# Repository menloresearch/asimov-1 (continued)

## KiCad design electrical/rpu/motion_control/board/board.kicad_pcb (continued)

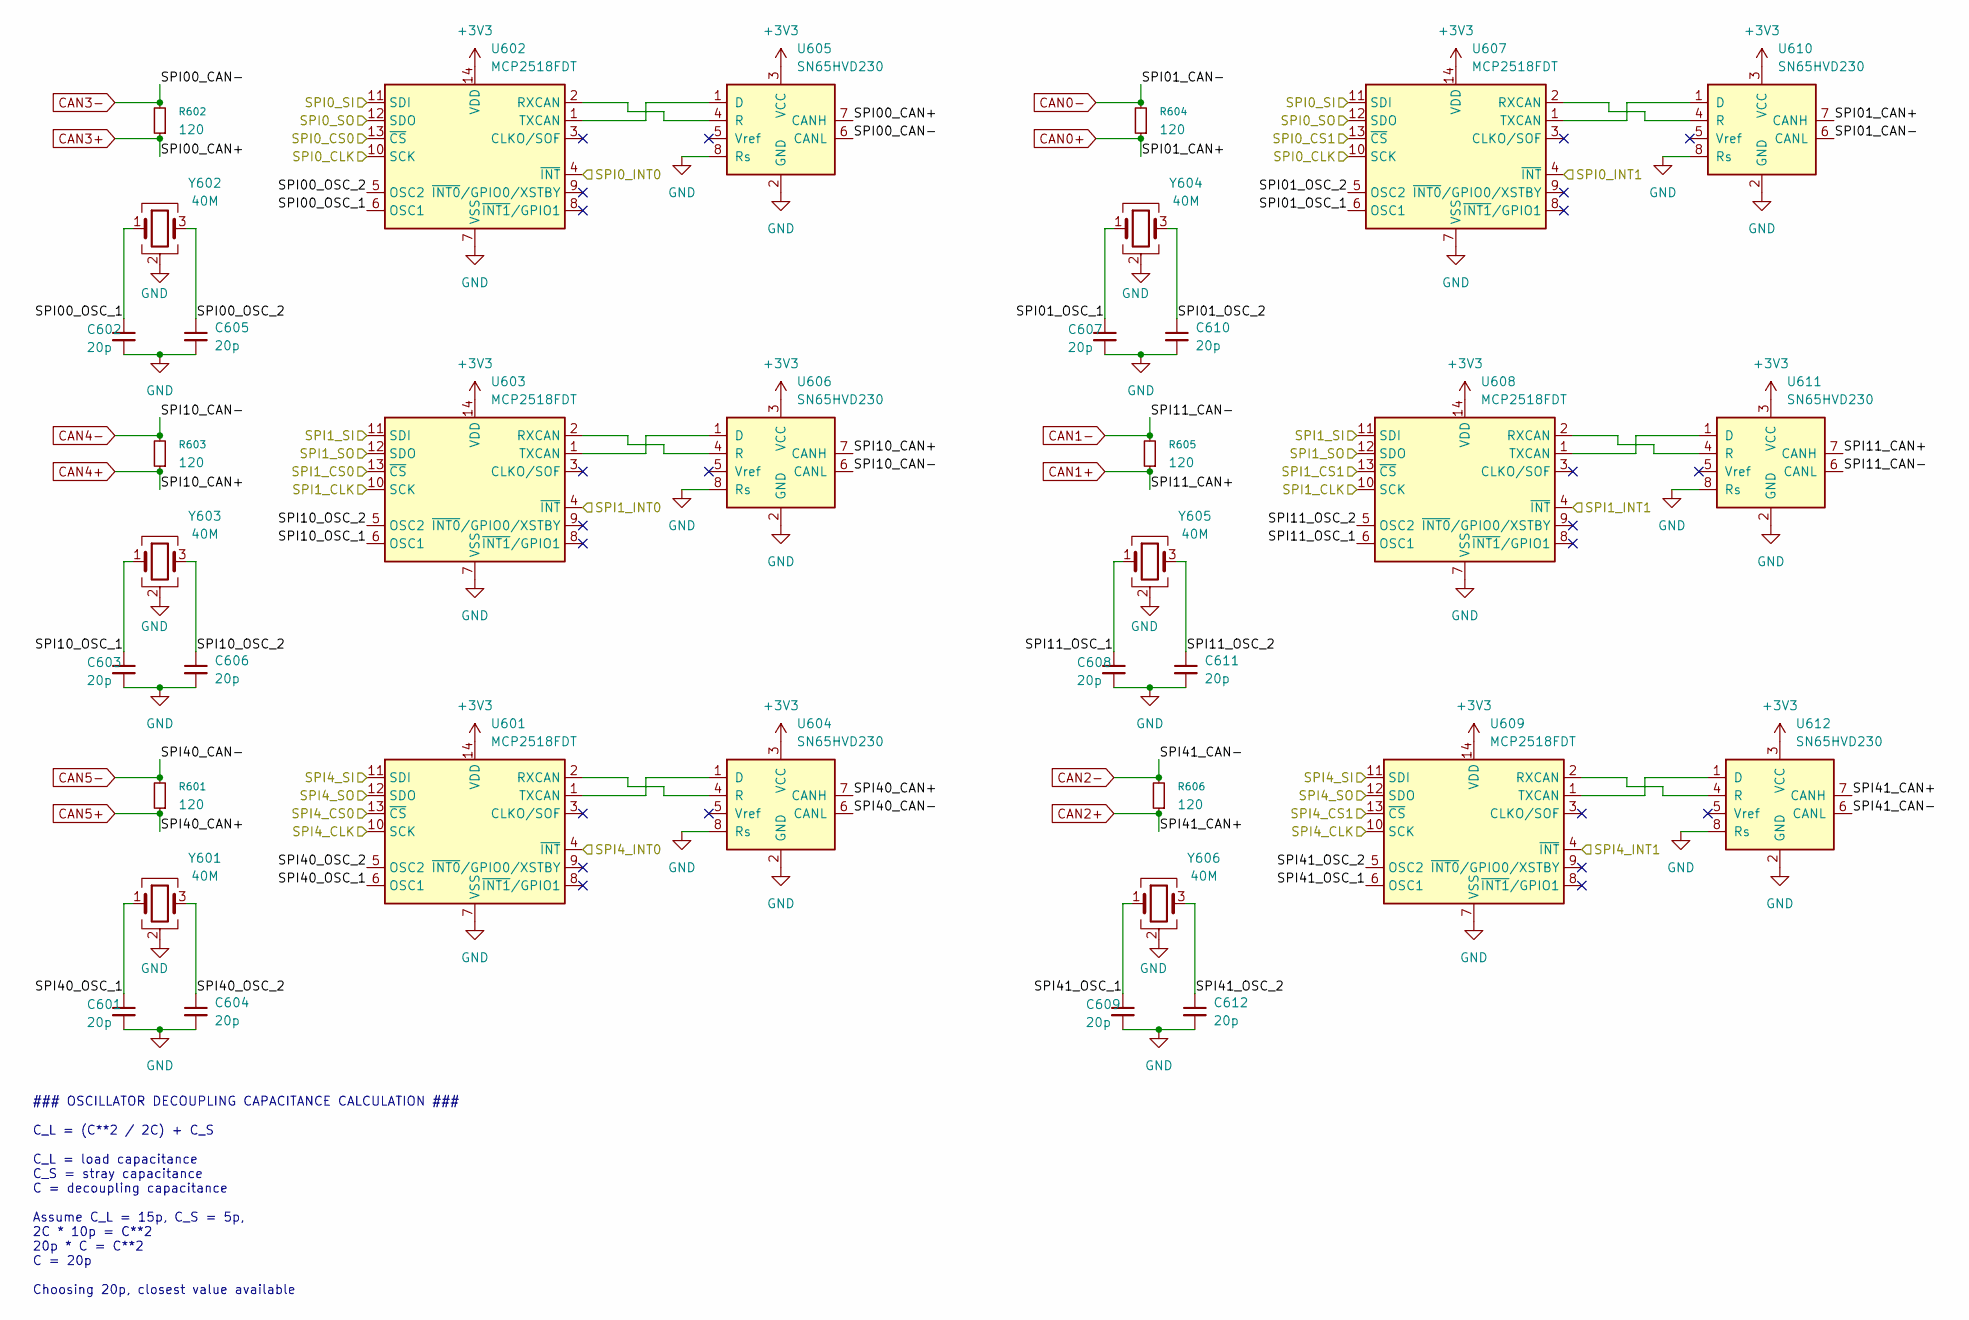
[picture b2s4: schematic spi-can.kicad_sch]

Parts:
C601, C602, C603, C604, C605, C606, C607, C608, C609, C610, C611, C612: 20p; C_0603_1608Metric; LCSC C165732
R601, R602, R603, R604, R605, R606: 120; R_0402_1005Metric; LCSC C114758
U601, U602, U603, U607, U608, U609: MCP2518FDT; SOIC-14_3.9x8.7mm_P1.27mm
U604, U605, U606, U610, U611, U612: SN65HVD230; SOIC-8_3.9x4.9mm_P1.27mm; LCSC C12084
Y601, Y602, Y603, Y604, Y605, Y606: 40M; Crystal_SMD_3225-4Pin_3.2x2.5mm; LCSC C7473041

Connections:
+3V3: U601.14 (VDD), U602.14 (VDD), U603.14 (VDD), U604.3 (VCC), U605.3 (VCC), U606.3 (VCC), U607.14 (VDD), U608.14 (VDD), U609.14 (VDD), U610.3 (VCC), U611.3 (VCC), U612.3 (VCC); also elsewhere on the board
/J1/SPI1_CS0: U603.13 (~CS); also elsewhere on the board
/J1/SPI1_CS1: U608.13 (~CS); also elsewhere on the board
/J1/SPI1_INT0: U603.4 (~INT); also elsewhere on the board
/J1/SPI1_INT1: U608.4 (~INT); also elsewhere on the board
/J1/SPI4_CS0: U601.13 (~CS); also elsewhere on the board
/J1/SPI4_CS1: U609.13 (~CS); also elsewhere on the board
/J1/SPI4_INT0: U601.4 (~INT); also elsewhere on the board
/J1/SPI4_INT1: U609.4 (~INT); also elsewhere on the board
/SPI-CAN/SPI0_CLK: U602.10 (SCK), U607.10 (SCK); also elsewhere on the board
/SPI-CAN/SPI0_CS0: U602.13 (~CS); also elsewhere on the board
/SPI-CAN/SPI0_CS1: U607.13 (~CS); also elsewhere on the board
/SPI-CAN/SPI0_INT0: U602.4 (~INT); also elsewhere on the board
/SPI-CAN/SPI0_INT1: U607.4 (~INT); also elsewhere on the board
/SPI-CAN/SPI00_OSC_1: C602.1, U602.6 (OSC1), Y602.1
/SPI-CAN/SPI00_OSC_2: C605.1, U602.5 (OSC2), Y602.3
/SPI-CAN/SPI0_SI: U602.11 (SDI), U607.11 (SDI); also elsewhere on the board
/SPI-CAN/SPI0_SO: U602.12 (SDO), U607.12 (SDO); also elsewhere on the board
/SPI-CAN/SPI1_CLK: U603.10 (SCK), U608.10 (SCK); also elsewhere on the board
/SPI-CAN/SPI01_OSC_1: C607.1, U607.6 (OSC1), Y604.1
/SPI-CAN/SPI01_OSC_2: C610.1, U607.5 (OSC2), Y604.3
/SPI-CAN/SPI1_SI: U603.11 (SDI), U608.11 (SDI); also elsewhere on the board
/SPI-CAN/SPI1_SO: U603.12 (SDO), U608.12 (SDO); also elsewhere on the board
/SPI-CAN/SPI4_CLK: U601.10 (SCK), U609.10 (SCK); also elsewhere on the board
/SPI-CAN/SPI4_SI: U601.11 (SDI), U609.11 (SDI); also elsewhere on the board
/SPI-CAN/SPI4_SO: U601.12 (SDO), U609.12 (SDO); also elsewhere on the board
/SPI-CAN/SPI10_OSC_1: C603.1, U603.6 (OSC1), Y603.1
/SPI-CAN/SPI10_OSC_2: C606.1, U603.5 (OSC2), Y603.3
/SPI-CAN/SPI11_OSC_1: C608.1, U608.6 (OSC1), Y605.1
/SPI-CAN/SPI11_OSC_2: C611.1, U608.5 (OSC2), Y605.3
/SPI-CAN/SPI40_OSC_1: C601.1, U601.6 (OSC1), Y601.1
/SPI-CAN/SPI40_OSC_2: C604.1, U601.5 (OSC2), Y601.3
/SPI-CAN/SPI41_OSC_1: C609.1, U609.6 (OSC1), Y606.1
/SPI-CAN/SPI41_OSC_2: C612.1, U609.5 (OSC2), Y606.3
CAN0+: R604.1, U610.7 (CANH); also elsewhere on the board
CAN0-: R604.2, U610.6 (CANL); also elsewhere on the board
CAN1+: R605.1, U611.7 (CANH); also elsewhere on the board
CAN1-: R605.2, U611.6 (CANL); also elsewhere on the board
CAN2+: R606.1, U612.7 (CANH); also elsewhere on the board
CAN2-: R606.2, U612.6 (CANL); also elsewhere on the board
CAN3+: R602.1, U605.7 (CANH); also elsewhere on the board
CAN3-: R602.2, U605.6 (CANL); also elsewhere on the board
CAN4+: R603.1, U606.7 (CANH); also elsewhere on the board
CAN4-: R603.2, U606.6 (CANL); also elsewhere on the board
CAN5+: R601.1, U604.7 (CANH); also elsewhere on the board
CAN5-: R601.2, U604.6 (CANL); also elsewhere on the board
GND: C601.2, C602.2, C603.2, C604.2, C605.2, C606.2, C607.2, C608.2, C609.2, C610.2, C611.2, C612.2, U601.7 (VSS), U601.15 (VSS), U602.7 (VSS), U602.15 (VSS), U603.7 (VSS), U603.15 (VSS), U604.2 (GND), U604.8 (Rs), U605.2 (GND), U605.8 (Rs), U606.2 (GND), U606.8 (Rs), U607.7 (VSS), U607.15 (VSS), U608.7 (VSS), U608.15 (VSS), U609.7 (VSS), U609.15 (VSS), U610.2 (GND), U610.8 (Rs), U611.2 (GND), U611.8 (Rs), U612.2 (GND), U612.8 (Rs), Y601.2 (G), Y601.4 (G), Y602.2 (G), Y602.4 (G), Y603.2 (G), Y603.4 (G), Y604.2 (G), Y604.4 (G), Y605.2 (G), Y605.4 (G), Y606.2 (G), Y606.4 (G); also elsewhere on the board
unnamed: U601.2 (RXCAN), U604.4 (R)
unnamed: U601.1 (TXCAN), U604.1 (D)
unnamed: U602.2 (RXCAN), U605.4 (R)
unnamed: U602.1 (TXCAN), U605.1 (D)
unnamed: U603.2 (RXCAN), U606.4 (R)
unnamed: U603.1 (TXCAN), U606.1 (D)
unnamed: U607.2 (RXCAN), U610.4 (R)
unnamed: U607.1 (TXCAN), U610.1 (D)
unnamed: U608.2 (RXCAN), U611.4 (R)
unnamed: U608.1 (TXCAN), U611.1 (D)
unnamed: U609.2 (RXCAN), U612.4 (R)
unnamed: U609.1 (TXCAN), U612.1 (D)

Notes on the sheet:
### OSCILLATOR DECOUPLING CAPACITANCE CALCULATION ### C_L = (C**2 / 2C) + C_S C_L = load capacitance C_S = stray capacitance C = decoupling capacitance Assume C_L = 15p, C_S = 5p, 2C * 10p = C**2 20p * C = C**2 C = 20p Choosing 20p, closest value available

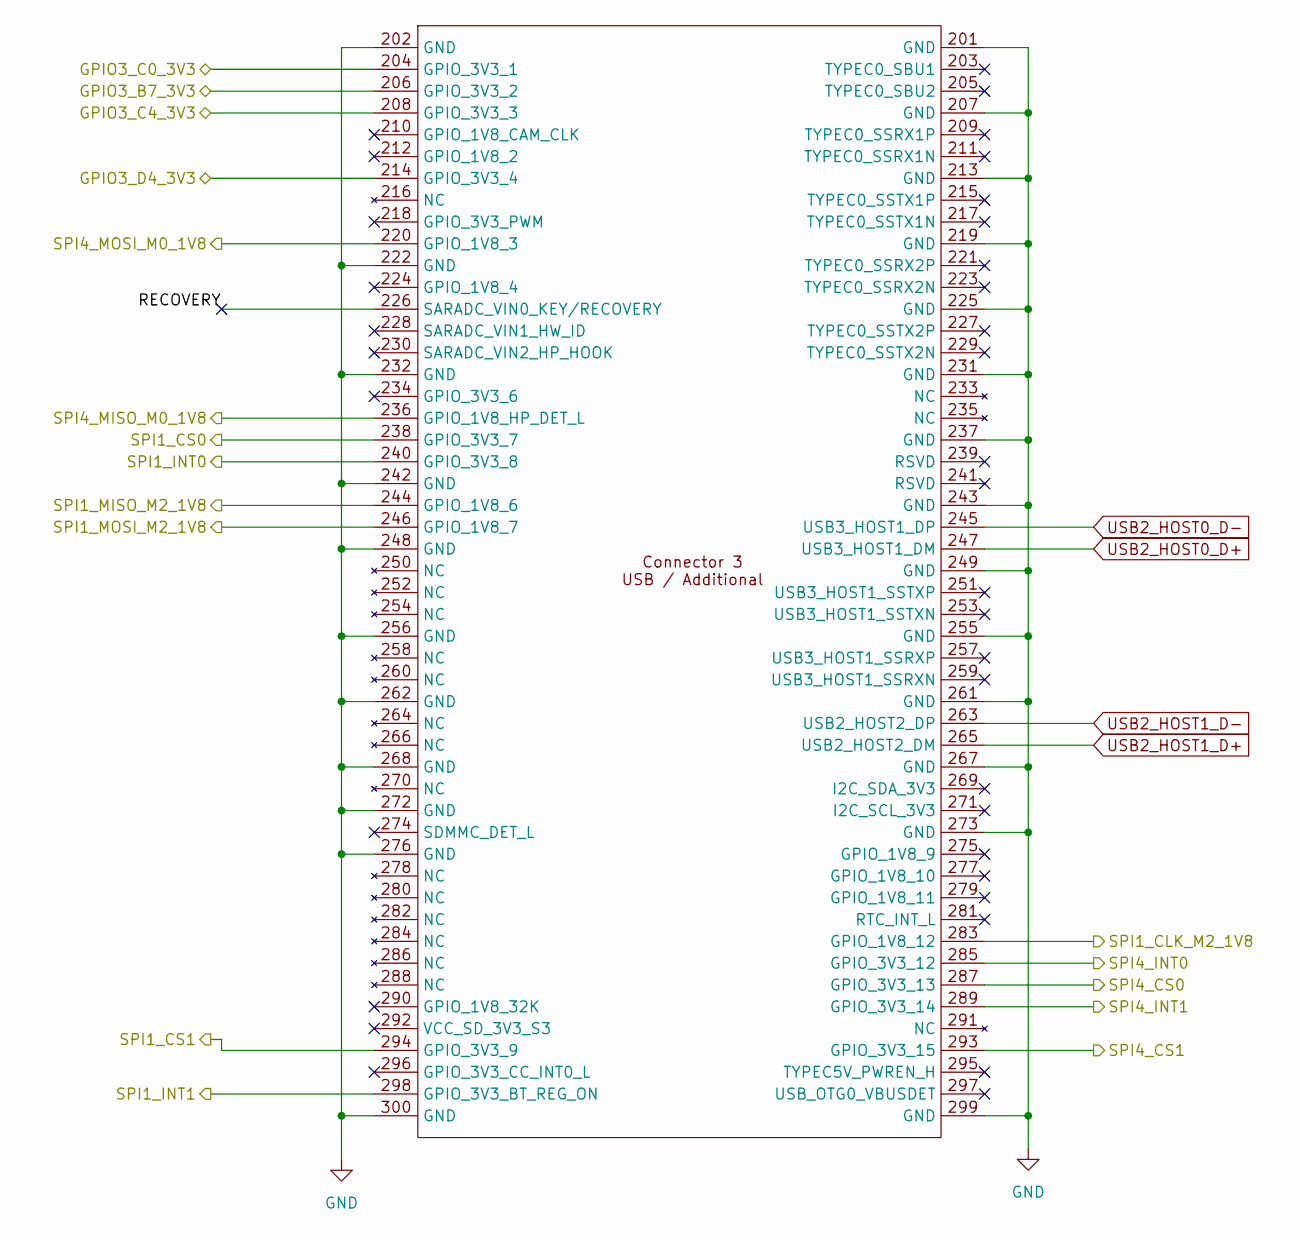
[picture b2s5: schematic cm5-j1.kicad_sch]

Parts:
U401: Hirose DF40C-100DS-0.4V; radxa_cm5_3; LCSC C597931

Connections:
/J1/GPIO3_B7_3V3: U401.206 (GPIO_3V3_2); also elsewhere on the board
/J1/GPIO3_C0_3V3: U401.204 (GPIO_3V3_1); also elsewhere on the board
/J1/GPIO3_C4_3V3: U401.208 (GPIO_3V3_3); also elsewhere on the board
/J1/GPIO3_D4_3V3: U401.214 (GPIO_3V3_4); also elsewhere on the board
/J1/RECOVERY: U401.226 (SARADC_VIN0_KEY/RECOVERY)
/J1/SPI1_CLK_M2_1V8: U401.283 (GPIO_1V8_12); also elsewhere on the board
/J1/SPI1_CS0: U401.238 (GPIO_3V3_7); also elsewhere on the board
/J1/SPI1_CS1: U401.294 (GPIO_3V3_9); also elsewhere on the board
/J1/SPI1_INT0: U401.240 (GPIO_3V3_8); also elsewhere on the board
/J1/SPI1_INT1: U401.298 (GPIO_3V3_BT_REG_ON); also elsewhere on the board
/J1/SPI1_MISO_M2_1V8: U401.244 (GPIO_1V8_6); also elsewhere on the board
/J1/SPI1_MOSI_M2_1V8: U401.246 (GPIO_1V8_7); also elsewhere on the board
/J1/SPI4_CS0: U401.287 (GPIO_3V3_13); also elsewhere on the board
/J1/SPI4_CS1: U401.293 (GPIO_3V3_15); also elsewhere on the board
/J1/SPI4_INT0: U401.285 (GPIO_3V3_12); also elsewhere on the board
/J1/SPI4_INT1: U401.289 (GPIO_3V3_14); also elsewhere on the board
/J1/SPI4_MISO_M0_1V8: U401.236 (GPIO_1V8_HP_DET_L); also elsewhere on the board
/J1/SPI4_MOSI_M0_1V8: U401.220 (GPIO_1V8_3); also elsewhere on the board
GND: U401.201 (GND), U401.202 (GND), U401.207 (GND), U401.213 (GND), U401.219 (GND), U401.222 (GND), U401.225 (GND), U401.231 (GND), U401.232 (GND), U401.237 (GND), U401.242 (GND), U401.243 (GND), U401.248 (GND), U401.249 (GND), U401.255 (GND), U401.256 (GND), U401.261 (GND), U401.262 (GND), U401.267 (GND), U401.268 (GND), U401.272 (GND), U401.273 (GND), U401.276 (GND), U401.299 (GND), U401.300 (GND); also elsewhere on the board
USB2_HOST0_D+: U401.247 (USB3_HOST1_DM); also elsewhere on the board
USB2_HOST0_D-: U401.245 (USB3_HOST1_DP); also elsewhere on the board
USB2_HOST1_D+: U401.265 (USB2_HOST2_DM); also elsewhere on the board
USB2_HOST1_D-: U401.263 (USB2_HOST2_DP); also elsewhere on the board

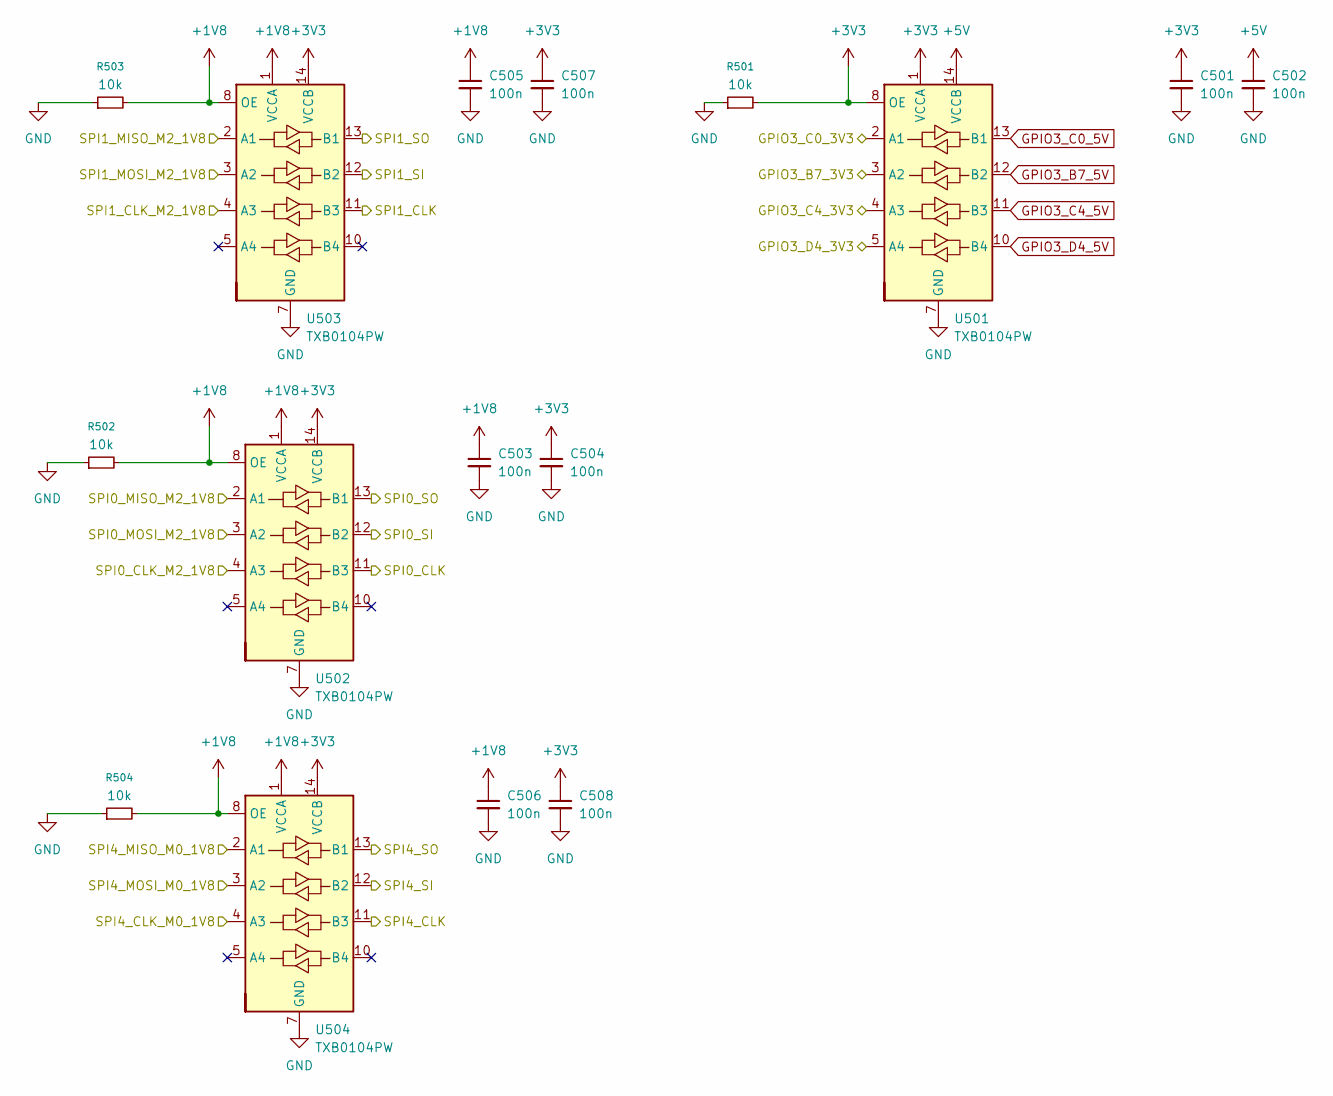
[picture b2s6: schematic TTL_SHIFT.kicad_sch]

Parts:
C501, C502, C503, C504, C505, C506, C507, C508: 100n; C_0402_1005Metric; LCSC C77020
R501, R502, R503, R504: 10k; R_0402_1005Metric; LCSC C190095
U501, U502, U503, U504: TXB0104PW; TSSOP-14_4.4x5mm_P0.65mm; LCSC C60708

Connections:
+1V8: C503.1, C505.1, C506.1, R502.2, R503.2, R504.2, U502.1 (VCCA), U502.8 (OE), U503.1 (VCCA), U503.8 (OE), U504.1 (VCCA), U504.8 (OE); also elsewhere on the board
+3V3: C501.1, C504.1, C507.1, C508.1, R501.2, U501.1 (VCCA), U501.8 (OE), U502.14 (VCCB), U503.14 (VCCB), U504.14 (VCCB); also elsewhere on the board
+5V: C502.1, U501.14 (VCCB); also elsewhere on the board
/J1/GPIO3_B7_3V3: U501.3 (A2); also elsewhere on the board
/J1/GPIO3_C0_3V3: U501.2 (A1); also elsewhere on the board
/J1/GPIO3_C4_3V3: U501.4 (A3); also elsewhere on the board
/J1/GPIO3_D4_3V3: U501.5 (A4); also elsewhere on the board
/J1/SPI1_CLK_M2_1V8: U503.4 (A3); also elsewhere on the board
/J1/SPI1_MISO_M2_1V8: U503.2 (A1); also elsewhere on the board
/J1/SPI1_MOSI_M2_1V8: U503.3 (A2); also elsewhere on the board
/J1/SPI4_MISO_M0_1V8: U504.2 (A1); also elsewhere on the board
/J1/SPI4_MOSI_M0_1V8: U504.3 (A2); also elsewhere on the board
/SPI-CAN/SPI0_CLK: U502.11 (B3); also elsewhere on the board
/SPI-CAN/SPI0_SI: U502.12 (B2); also elsewhere on the board
/SPI-CAN/SPI0_SO: U502.13 (B1); also elsewhere on the board
/SPI-CAN/SPI1_CLK: U503.11 (B3); also elsewhere on the board
/SPI-CAN/SPI1_SI: U503.12 (B2); also elsewhere on the board
/SPI-CAN/SPI1_SO: U503.13 (B1); also elsewhere on the board
/SPI-CAN/SPI4_CLK: U504.11 (B3); also elsewhere on the board
/SPI-CAN/SPI4_SI: U504.12 (B2); also elsewhere on the board
/SPI-CAN/SPI4_SO: U504.13 (B1); also elsewhere on the board
/TTL-SHIFT/SPI0_CLK_M2_1V8: U502.4 (A3); also elsewhere on the board
/TTL-SHIFT/SPI0_MISO_M2_1V8: U502.2 (A1); also elsewhere on the board
/TTL-SHIFT/SPI0_MOSI_M2_1V8: U502.3 (A2); also elsewhere on the board
/TTL-SHIFT/SPI4_CLK_M0_1V8: U504.4 (A3); also elsewhere on the board
GND: C501.2, C502.2, C503.2, C504.2, C505.2, C506.2, C507.2, C508.2, R501.1, R502.1, R503.1, R504.1, U501.7 (GND), U502.7 (GND), U503.7 (GND), U504.7 (GND); also elsewhere on the board
GPIO3_B7_5V: U501.12 (B2); also elsewhere on the board
GPIO3_C0_5V: U501.13 (B1); also elsewhere on the board
GPIO3_C4_5V: U501.11 (B3); also elsewhere on the board
GPIO3_D4_5V: U501.10 (B4); also elsewhere on the board

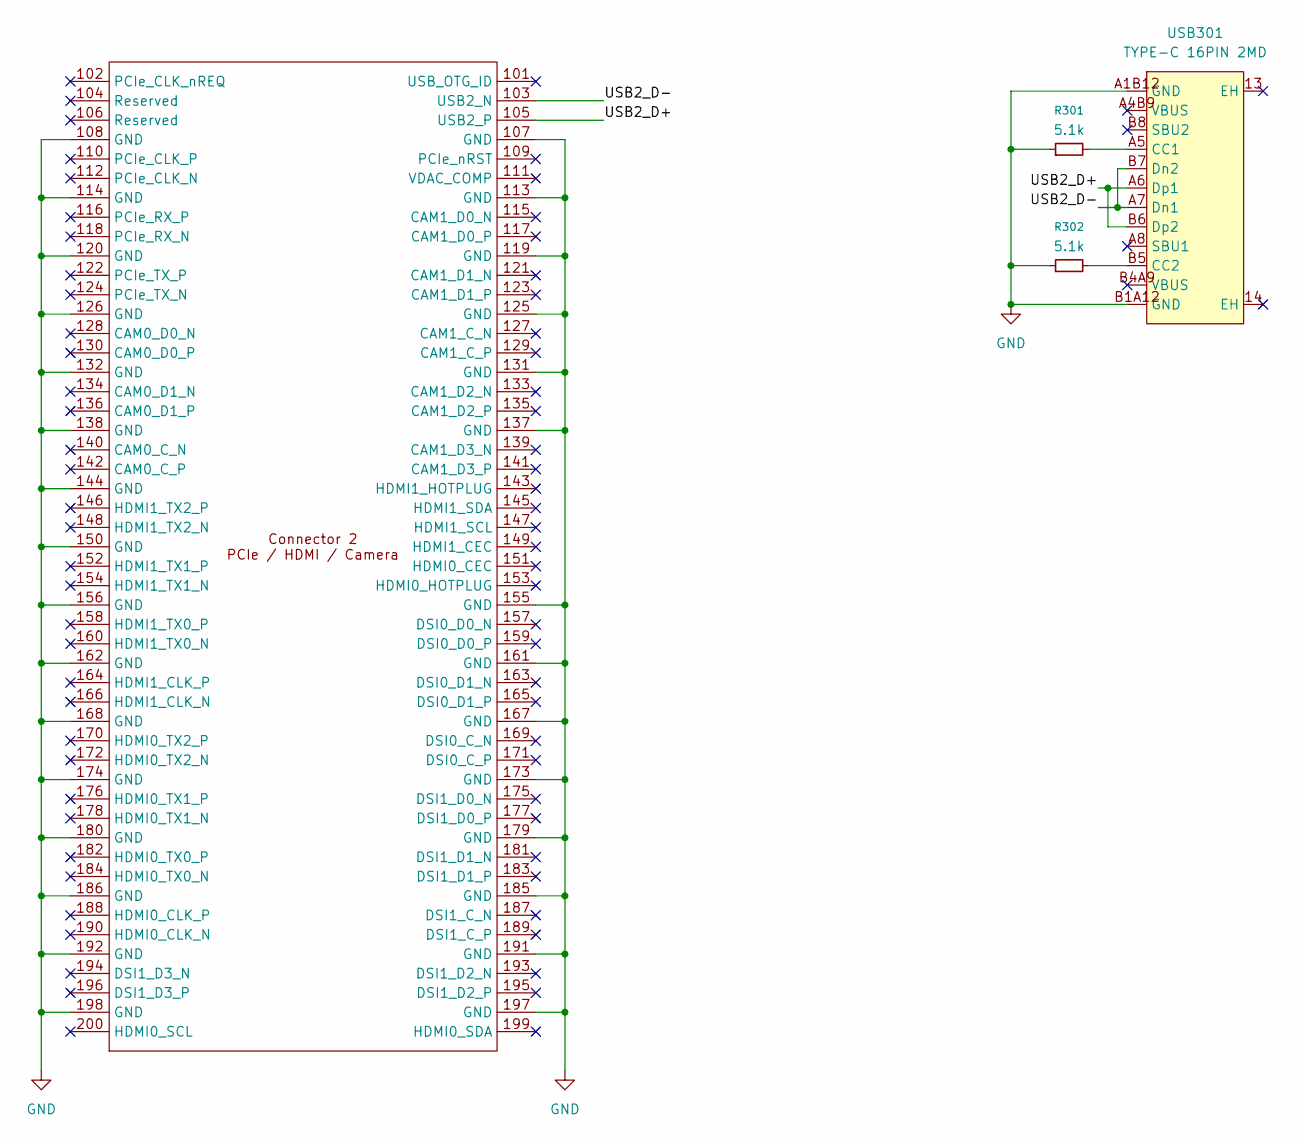
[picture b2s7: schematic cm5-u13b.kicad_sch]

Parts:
R301, R302: 5.1k; R_0402_1005Metric; LCSC C105872
U301: Hirose DF40C-100DS-0.4V; radxa_cm5_2; LCSC C597931
USB301: TYPE-C 16PIN 2MD; USB-C-SMD_TYPE-C-16PIN-2MD-073; MPN TYPE-C 16PIN 2MD(073); LCSC Part C2765186

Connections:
/U13B/USB2_D+: U301.105 (USB2_P), USB301.A6 (Dp1), USB301.B6 (Dp2)
/U13B/USB2_D-: U301.103 (USB2_N), USB301.A7 (Dn1), USB301.B7 (Dn2)
GND: R301.1, R302.1, U301.107 (GND), U301.108 (GND), U301.113 (GND), U301.114 (GND), U301.119 (GND), U301.120 (GND), U301.125 (GND), U301.126 (GND), U301.131 (GND), U301.132 (GND), U301.137 (GND), U301.138 (GND), U301.144 (GND), U301.150 (GND), U301.155 (GND), U301.156 (GND), U301.161 (GND), U301.162 (GND), U301.167 (GND), U301.168 (GND), U301.173 (GND), U301.174 (GND), U301.179 (GND), U301.180 (GND), U301.185 (GND), U301.186 (GND), U301.191 (GND), U301.192 (GND), U301.197 (GND), U301.198 (GND), USB301.A1B12 (GND), USB301.B1A12 (GND); also elsewhere on the board
unnamed: R301.2, USB301.A5 (CC1)
unnamed: R302.2, USB301.B5 (CC2)

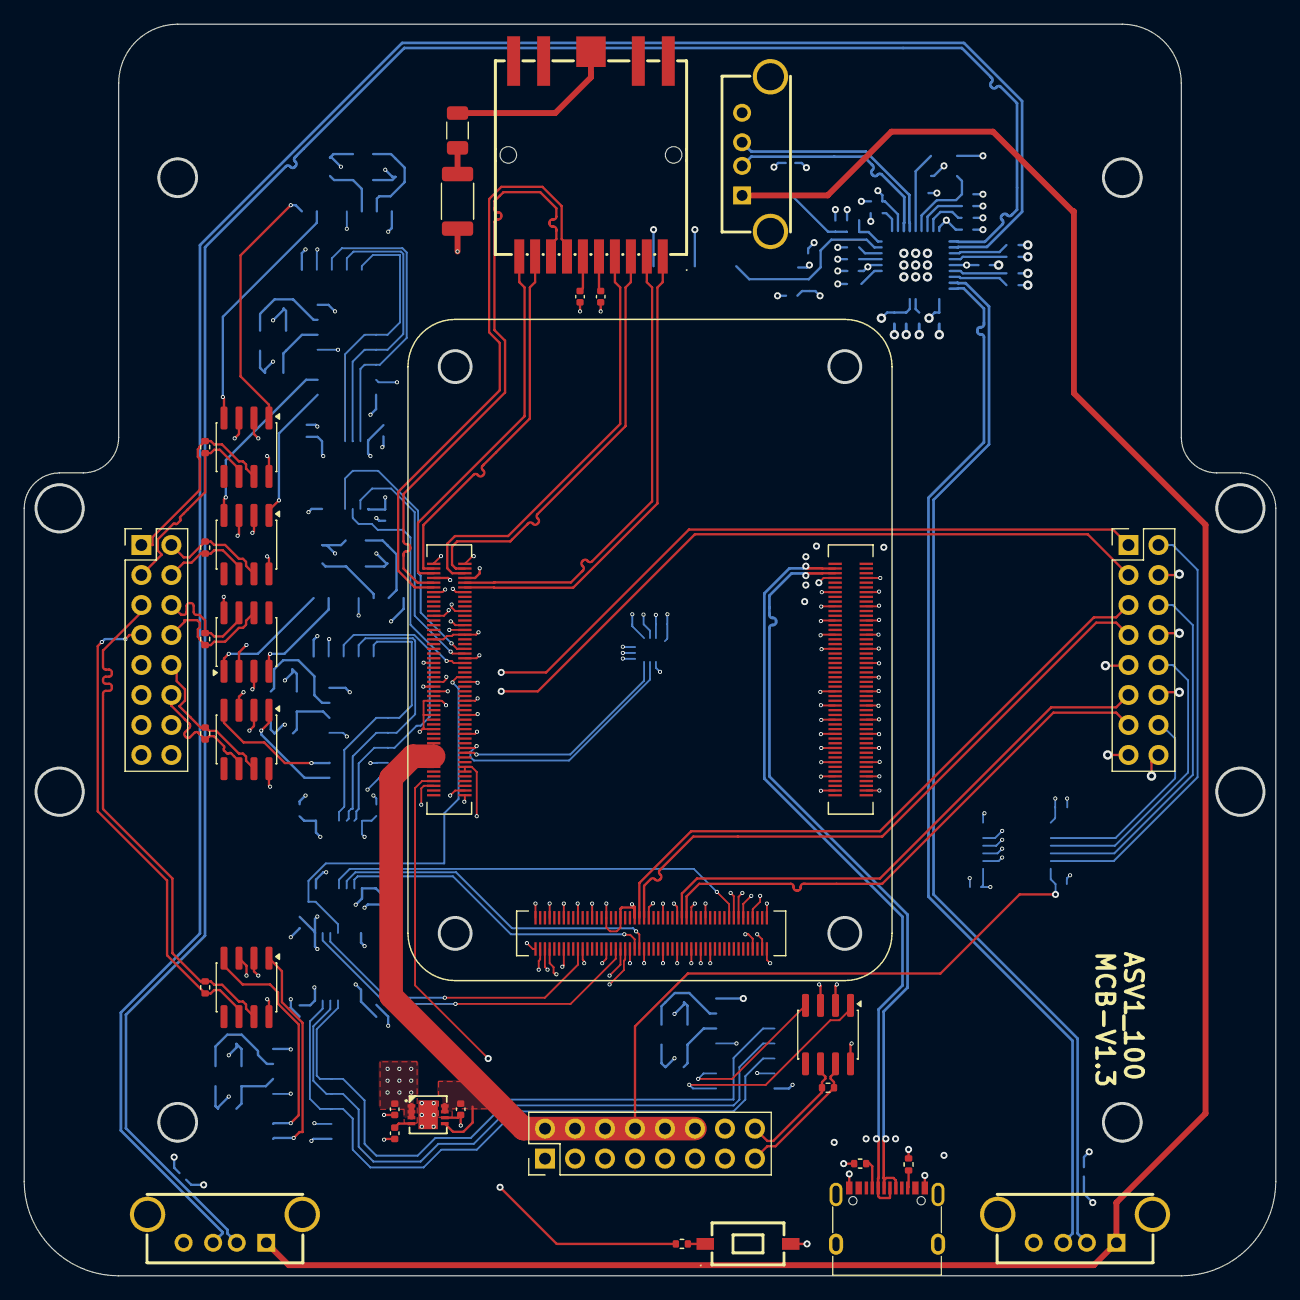
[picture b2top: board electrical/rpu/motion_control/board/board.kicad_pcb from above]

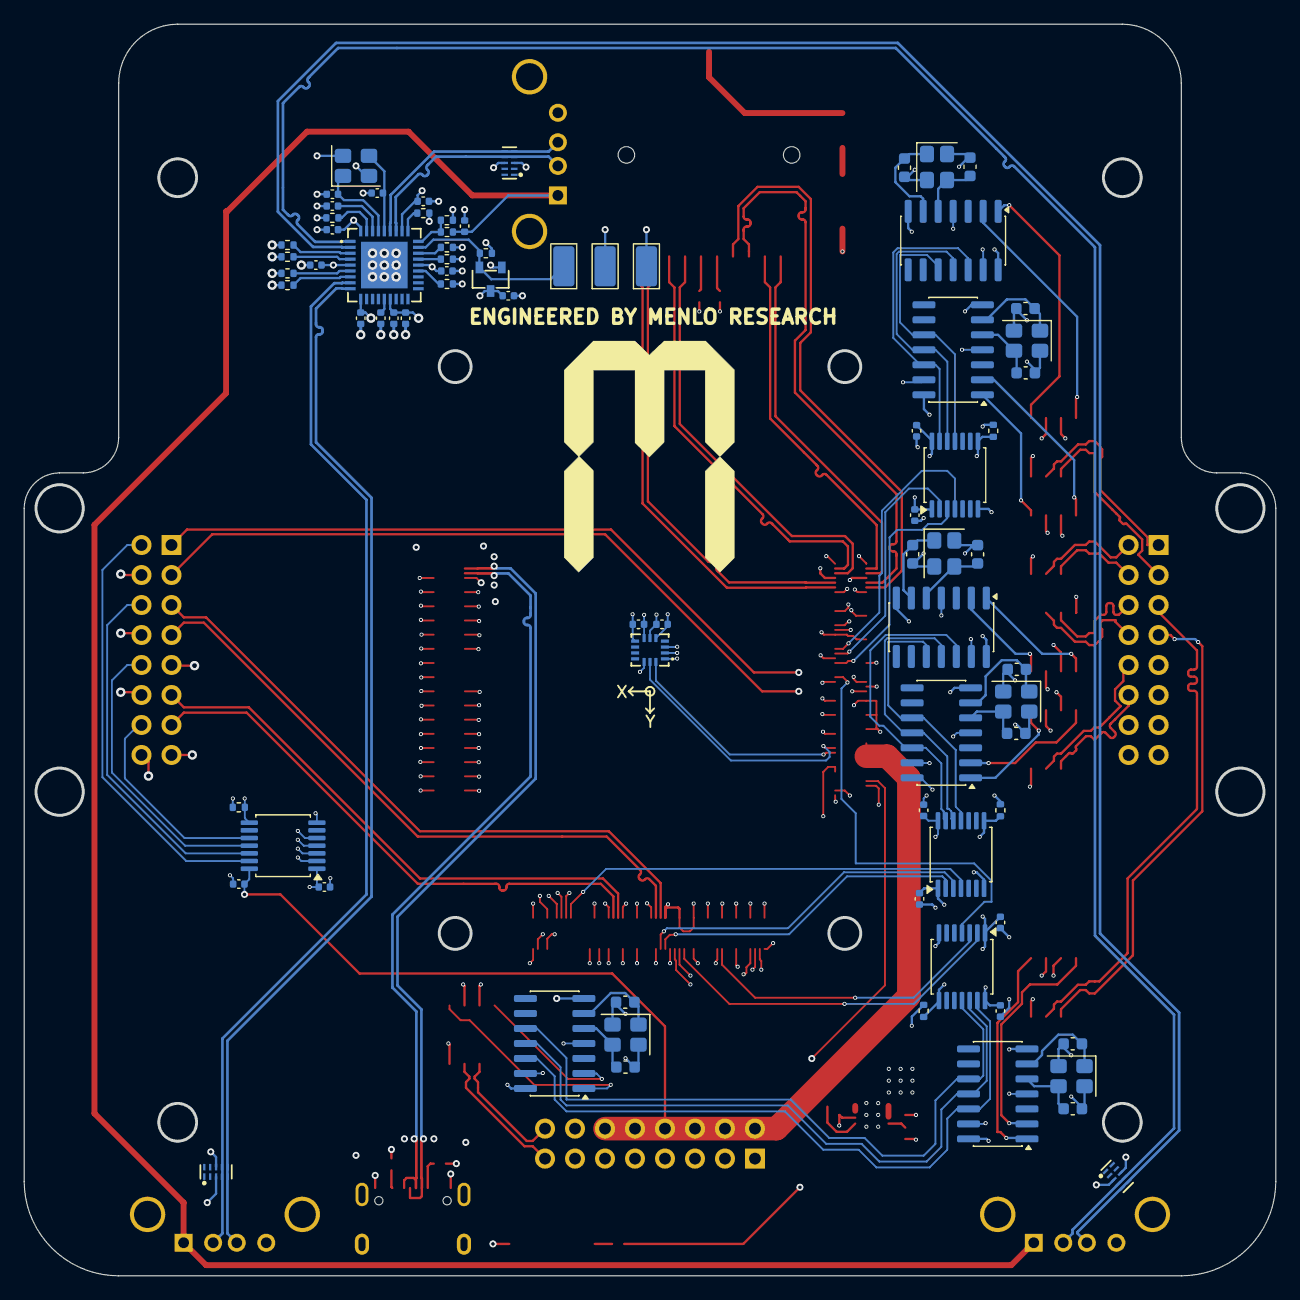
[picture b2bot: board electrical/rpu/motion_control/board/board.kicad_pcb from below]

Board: 4 copper layers, 106.0 x 106.0 mm, 112 parts (77 on the bottom side), 127 nets.

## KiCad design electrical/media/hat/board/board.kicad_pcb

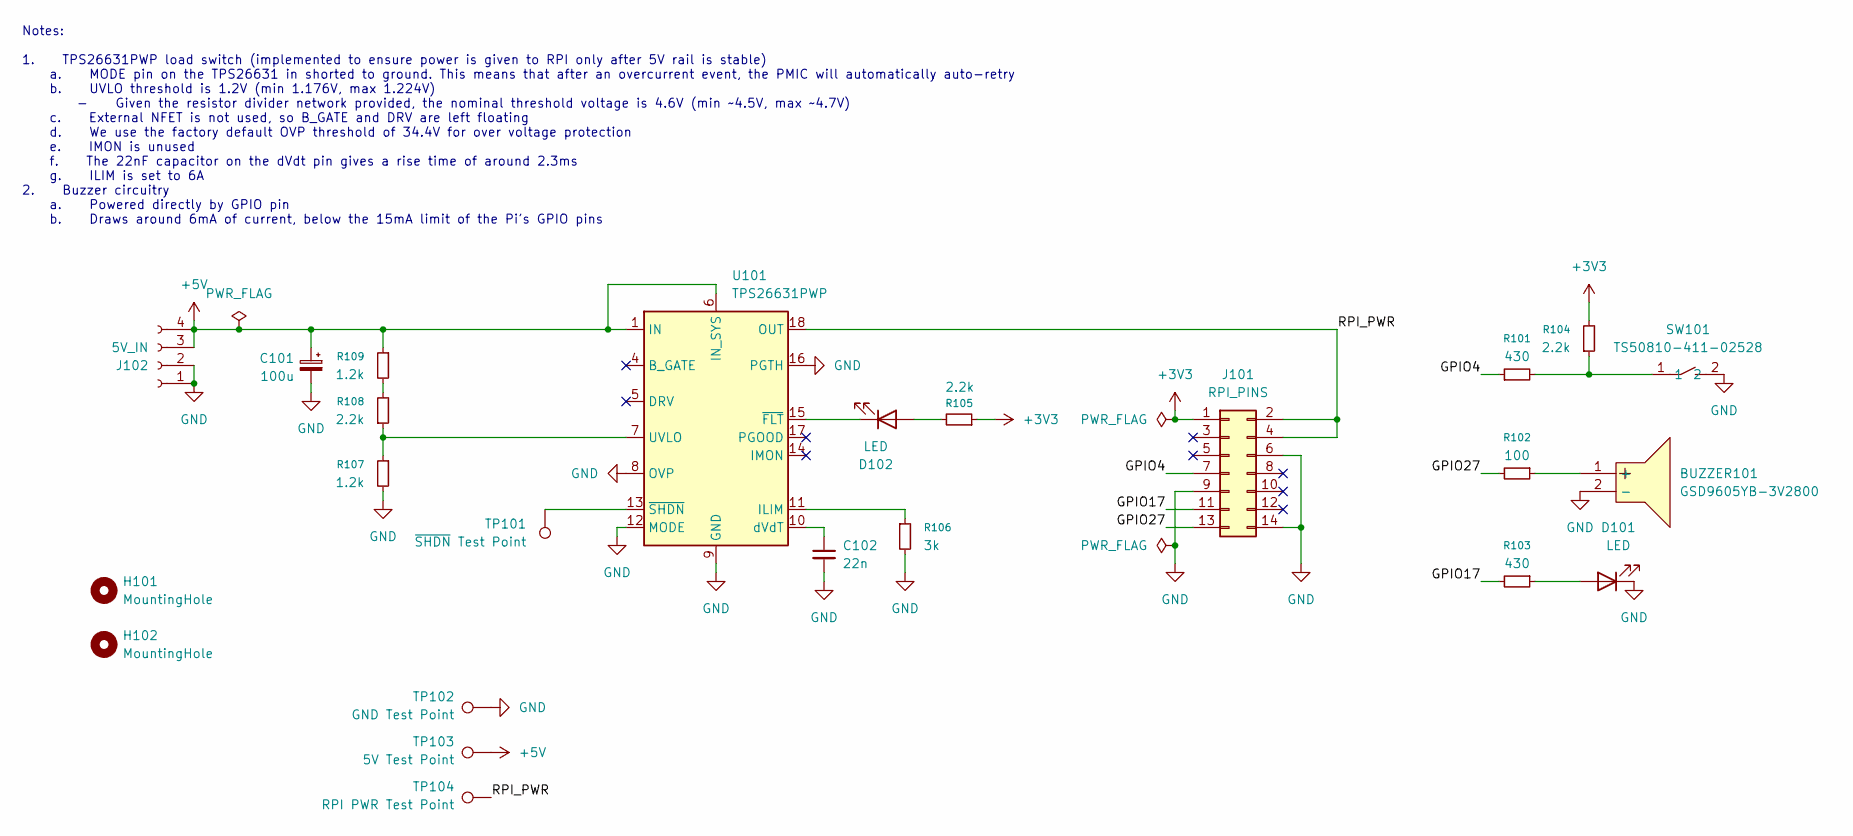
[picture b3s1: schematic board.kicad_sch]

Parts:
BUZZER101: GSD9605YB-3V2800; BUZ-SMD_GSD9605YB-3V2800; MPN GSD9605YB-3V2800; LCSC Part C255327
C101: 100u; CP_EIA-7343-31_Kemet-D; LCSC C600555
C102: 22n; C_0402_1005Metric; LCSC C1532
D101, D102: LED; LED_0603_1608Metric; LCSC C965804
H101, H102: MountingHole; MountingHole_2.5mm
J101: RPI_PINS; PinSocket_2x07_P2.54mm_Vertical; LCSC C5116484
J102: 5V_IN; JST_XH_B4B-XH-A_1x04_P2.50mm_Vertical; LCSC C144395
R101, R103: 430; R_0402_1005Metric; LCSC C137868
R102: 100; R_0402_1005Metric; LCSC C25076
R104, R105, R108: 2.2k; R_0402_1005Metric; LCSC C25879
R106: 3k; R_0603_1608Metric; LCSC C4211
R107, R109: 1.2k; R_0402_1005Metric; LCSC C2909307
SW101: TS50810-411-02528; SW-SMD_L6.2-W3.7-LS8.0; MPN TS50810-411-02528; LCSC Part C42400876
TP101: ~{SHDN} Test Point; TestPoint_Keystone_5015_Micro_Mini; LCSC C5199798
TP102: GND Test Point; TestPoint_Keystone_5015_Micro_Mini; LCSC C5199798
TP103: 5V Test Point; TestPoint_Keystone_5015_Micro_Mini; LCSC C5199798
TP104: RPI PWR Test Point; TestPoint_Keystone_5015_Micro_Mini; LCSC C5199798
U101: TPS26631PWP; HTSSOP-20-1EP_4.4x6.5mm_P0.65mm_EP3.4x6.5mm_Mask2.96x2.96mm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; LCSC C2866319

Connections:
+3V3: J101.1, R104.2, R105.1
+5V: C101.1, J102.3, J102.4, R109.1, TP103.1 (1_1), U101.1 (IN), U101.2 (IN), U101.3 (IN), U101.6 (IN_SYS)
/GPIO4: J101.7, R101.1
/GPIO17: J101.11, R103.2
/GPIO27: J101.13, R102.2
/RPI_PWR: J101.2, J101.4, TP104.1 (1_1), U101.18 (OUT), U101.19 (OUT), U101.20 (OUT)
GND: BUZZER101.2 (-), C101.2, C102.2, D101.1 (K), J101.6, J101.9, J101.14, J102.1, J102.2, R106.2, R107.2, SW101.2, TP102.1 (1_1), U101.8 (OVP), U101.9 (GND), U101.12 (MODE), U101.16 (PGTH), U101.21 (GND)
unnamed: BUZZER101.1 (+), R102.1
unnamed: D101.2 (A), R103.1
unnamed: D102.2 (A), R105.2
unnamed: D102.1 (K), U101.15 (~FLT)
unnamed: R101.2, R104.1, SW101.1
unnamed: R108.2, R109.2
unnamed: R106.1, U101.11 (ILIM)
unnamed: R107.1, R108.1, U101.7 (UVLO)
unnamed: C102.1, U101.10 (dVdT)
unnamed: TP101.1 (1_1), U101.13 (~SHDN)

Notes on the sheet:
Notes: 1. TPS26631PWP load switch (implemented to ensure power is given to RPI only after 5V rail is stable) a. MODE pin on the TPS26631 in shorted to ground. This means that after an overcurrent event, the PMIC will automatically auto-retry b. UVLO threshold is 1.2V (min 1.176V, max 1.224V) - Give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

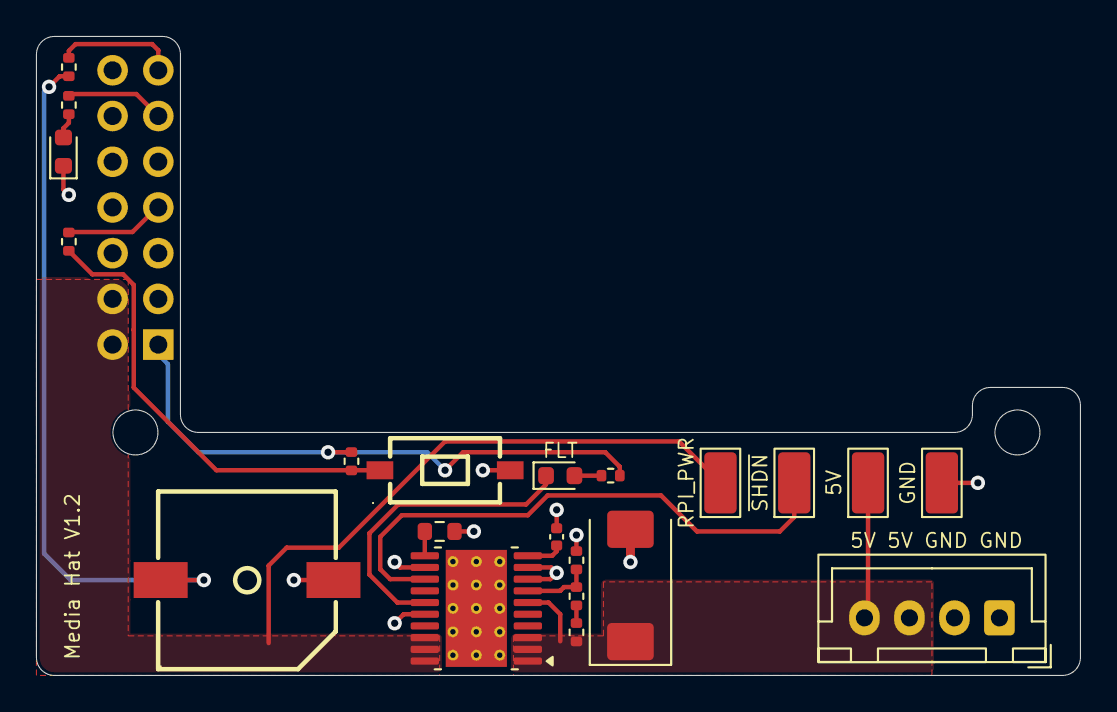
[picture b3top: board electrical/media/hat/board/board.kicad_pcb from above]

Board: 2 copper layers, 58.0 x 35.5 mm, 24 parts (1 on the bottom side), 17 nets.
